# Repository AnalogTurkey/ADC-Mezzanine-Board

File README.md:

# ADC Mezzanine Board
 ADS7886 ADC Mezzanine Board for PHYS150

 KiCad PCB files are contained in the "ads7886_PCB" folder. If you do not have KiCad, see the "images" folder for the schematic and PCB. "ADC_Reader.py" is a basic python script for interfacing with the ADC board using a Raspberry Pi.
 
 ## The Hardware
 
The board has 4 main sections: power supply, analog input, digital input ("CS timing"), and ADC. 

#### Power Supply:
Power is regulated to 3.3V from the 5V board connectors. This circuit is about as boring as it gets. There isn't even a dedicated output capacitor on the LDO since the loads' decoupling capacitors are so close to the output.

#### Analog Input:
The ADC itself, under ideal conditions, is capped at 1 MSPS (million samples per second), which means that it is too slow to measure the entirety of a pulse. The board uses a peak detector to isolate the maximum voltage of a given event instead. 

**R2** is a 100Ω trimpot which stabilizes the op-amp and isolates it from the capacitive load. If this value is too low, the peak detector may oscillate and overshoot the actual value of the peak. If it is too high, the capacitor may not charge quickly enough and the peak detector will undershoot. An ideal value is around 10-20Ω, though you may want to adjust it using the scope. 

**R4** and **C4** form an RC decay. The given values, 1nF and 1MΩ, correspond to a time constant of 1ms. The value of R4 may be lowered to make the voltage decay more quickly. It is preferable to tweak **R4** rather than **C4** because the capacitive load may change the behavior of the op-amp and schottky diode.

#### Digital Input:
The latch signal from the main board is the output of a one-shot which is triggered every time the input signal exceeds a certain threshold. However, the ADC itself takes a measurement when its CS input transitions from high to low. The latch signal is inverted (to make it function like CS) and delayed using **R3** and **C5** (so that measurements are always taken *after* the peak has passed. This delay corresponds to roughly 250ns to fall from logical high to logical low using the given values.
 
#### The ADC:
The datasheet for the ADS7886 is available [here](http://www.ti.com/lit/ds/symlink/ads7886.pdf). 

#### Test Points
There are 4 test points on the board. **CS** is the chip select (trigger) input to the ADC. **Vin** is the analog input to the ADC, the voltage that is being measured. **PD** is across the trimpot from **Vin**; measuring accross these two points will give the value of **R2**. **VDD** is connected to the mezzanine board's 3.3V power supply.

 ## The Software

 This script listens for output data from the ADC and saves it to a file named "ADC_Data.txt".
 As is, connect SCLK to pin 13, HOLD to pin 7, and SDO to pin 11. On the Pi, navigate in the terminal to the directory the script is in, then run "python ADC_Reader.py". 
 
 The code only saves data to the file every once in a while since accessing the file takes a nontrivial amount of time. This can be changed by changing the value of "BufferSize" in the code.
 
 The code is heavily commented, so for finer details it's probably better to check there. 
 
 ## Images

 In yellow is the raw signal. In purple is the 3.3V signal coming out of the Cosmic board's discriminator+oneshot. In cyan is the CS signal generated by the ADC: inverted, slightly RC-delayed, 5V.

 The peak detector ever-so-slightly undershoots the peak, which is the most ideal response. These images were taken from a modified board with a peak detector time constant of 10µs. Somewhat interesting is the appearance of a small blip in the analog signals at the same time as the digital transition, implying that the supplies (or the grounds) could have been better isolated.

 All of the above signals put together. Input signal in yellow, Peak Detector (test point VIN) in green, Oneshot in purple, CS in cyan.

 An ADC board installed, alongside another ADC board flipped upside down.

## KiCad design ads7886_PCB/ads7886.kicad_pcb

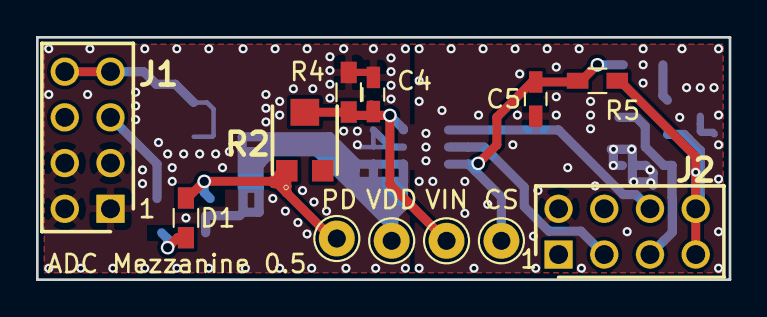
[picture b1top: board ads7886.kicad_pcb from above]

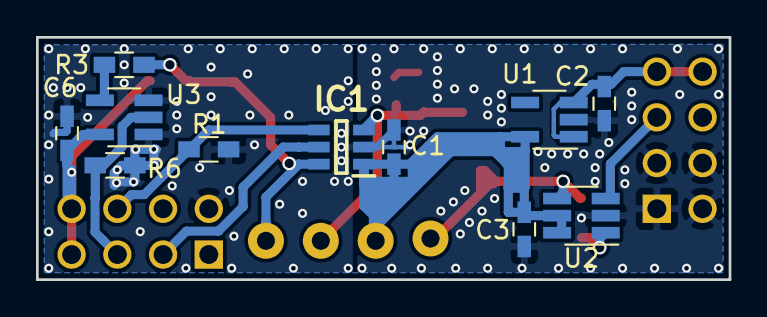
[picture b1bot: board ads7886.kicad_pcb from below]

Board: 2 copper layers, 38.5 x 13.5 mm, 23 parts (11 on the bottom side), 13 nets.

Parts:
C1, C2, C3, C6: 10u; C_0603_HandSoldering
C4, C5: 1n; C_0603_HandSoldering
CS: TEST; Pin_d1.0mm_L10.0mm
D1: BAT_63-02V_H6327; R_0603_HandSoldering
IC1: ADS7886SDBVT; SOT95P280X145-6N
J1, J2: 2214S-08SG-85; SHDR8W60P254_2X4_1016X508X850P
PD: TEST; Pin_d1.0mm_L10.0mm
R1, R5, R6: 10k; R_0603_HandSoldering
R2: TC33X-2-101E; TC33X-2_1
R3: 100; R_0603_HandSoldering
R4: 1M; R_0603_HandSoldering
U1: LP5907MFX-3.3; SOT-23-5_HandSoldering
U2: OPA355NA; SOT-23-6_Handsoldering
U3: 74LVC1G240; SOT-23-5_HandSoldering
VDD: TEST; Pin_d1.0mm_L10.0mm
VIN: TEST; Pin_d1.0mm_L10.0mm

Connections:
/5VA: C2.1, J1.7, J1.8, U1.1, U1.3
/CS: C5.1, CS.1, IC1.6, R3.1, R5.2
/LATCH: J2.5, R6.1, U3.2
/PD: D1.1, PD.1, R2.1, U2.4
/SCLK: IC1.4, J2.6, R1.1
/SDO: IC1.5, J2.3
/SIG_IN: J1.5, U2.3
/VDD: C1.1, C3.1, IC1.1, U1.5, U2.5, U2.6, VDD.1
/VIN: C4.1, IC1.3, R2.2, R4.1, VIN.1
GND: C1.2, C2.2, C3.2, C4.2, C5.2, C6.2, IC1.2, J1.1, J1.2, J1.3, J1.4, J2.2, R1.2, R4.2, R6.2, U1.2, U2.2, U3.1, U3.3
unnamed: D1.2, U2.1
unnamed: R3.2, U3.4
VCC: C6.1, J2.7, J2.8, R5.1, U3.5

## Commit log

2019-12-24 Edited script, added readme
    Changed GPIO assignment in script, added readme and scope image.
2019-12-24 Changed images
    Changed image order in readme.
    Changed image folder hierarchy.
2019-12-24 fixed typo in image links
2019-12-24 improved code comment readability
    Split very long comments into multiple lines, fixed typos.
2020-02-26 Improved PCB component compatilibity
    Widened LDO trace between IN and EN, mostly for aesthetics
    Grounded previously NC pad on inverter to allow for optional installation of 1G240 instead of 1G14
2020-02-26 Updated reader code
    Changed data detection to use more robust FIFO buffer
    Changed file output data format, now uses CSV style and saves in batches
2020-02-26 Updated images and README
    Changed some PCB images to reflect new version, added scope shots and additional elaboration to readme.
2020-02-26 Fixed readme images
    Changed file extensions to properly reference images in README
2020-02-26 changed more extensions
    Oops, wrong case!
2020-02-26 typo
2020-03-10 Fixed Python Code
    Changed default pins (clock, sdo, hold) from 31, 33, 29 to 13, 11, 7 to make the code compatible with the standalone ADC Pi board. These values can be changed back in the python file on lines 33-35 i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
    Fixed an issue where the CS line going low after toggling SCLK and sampling SDO would cause the data to be offset by one bit, by monitoring SDO asynchronously until the data word begins.
